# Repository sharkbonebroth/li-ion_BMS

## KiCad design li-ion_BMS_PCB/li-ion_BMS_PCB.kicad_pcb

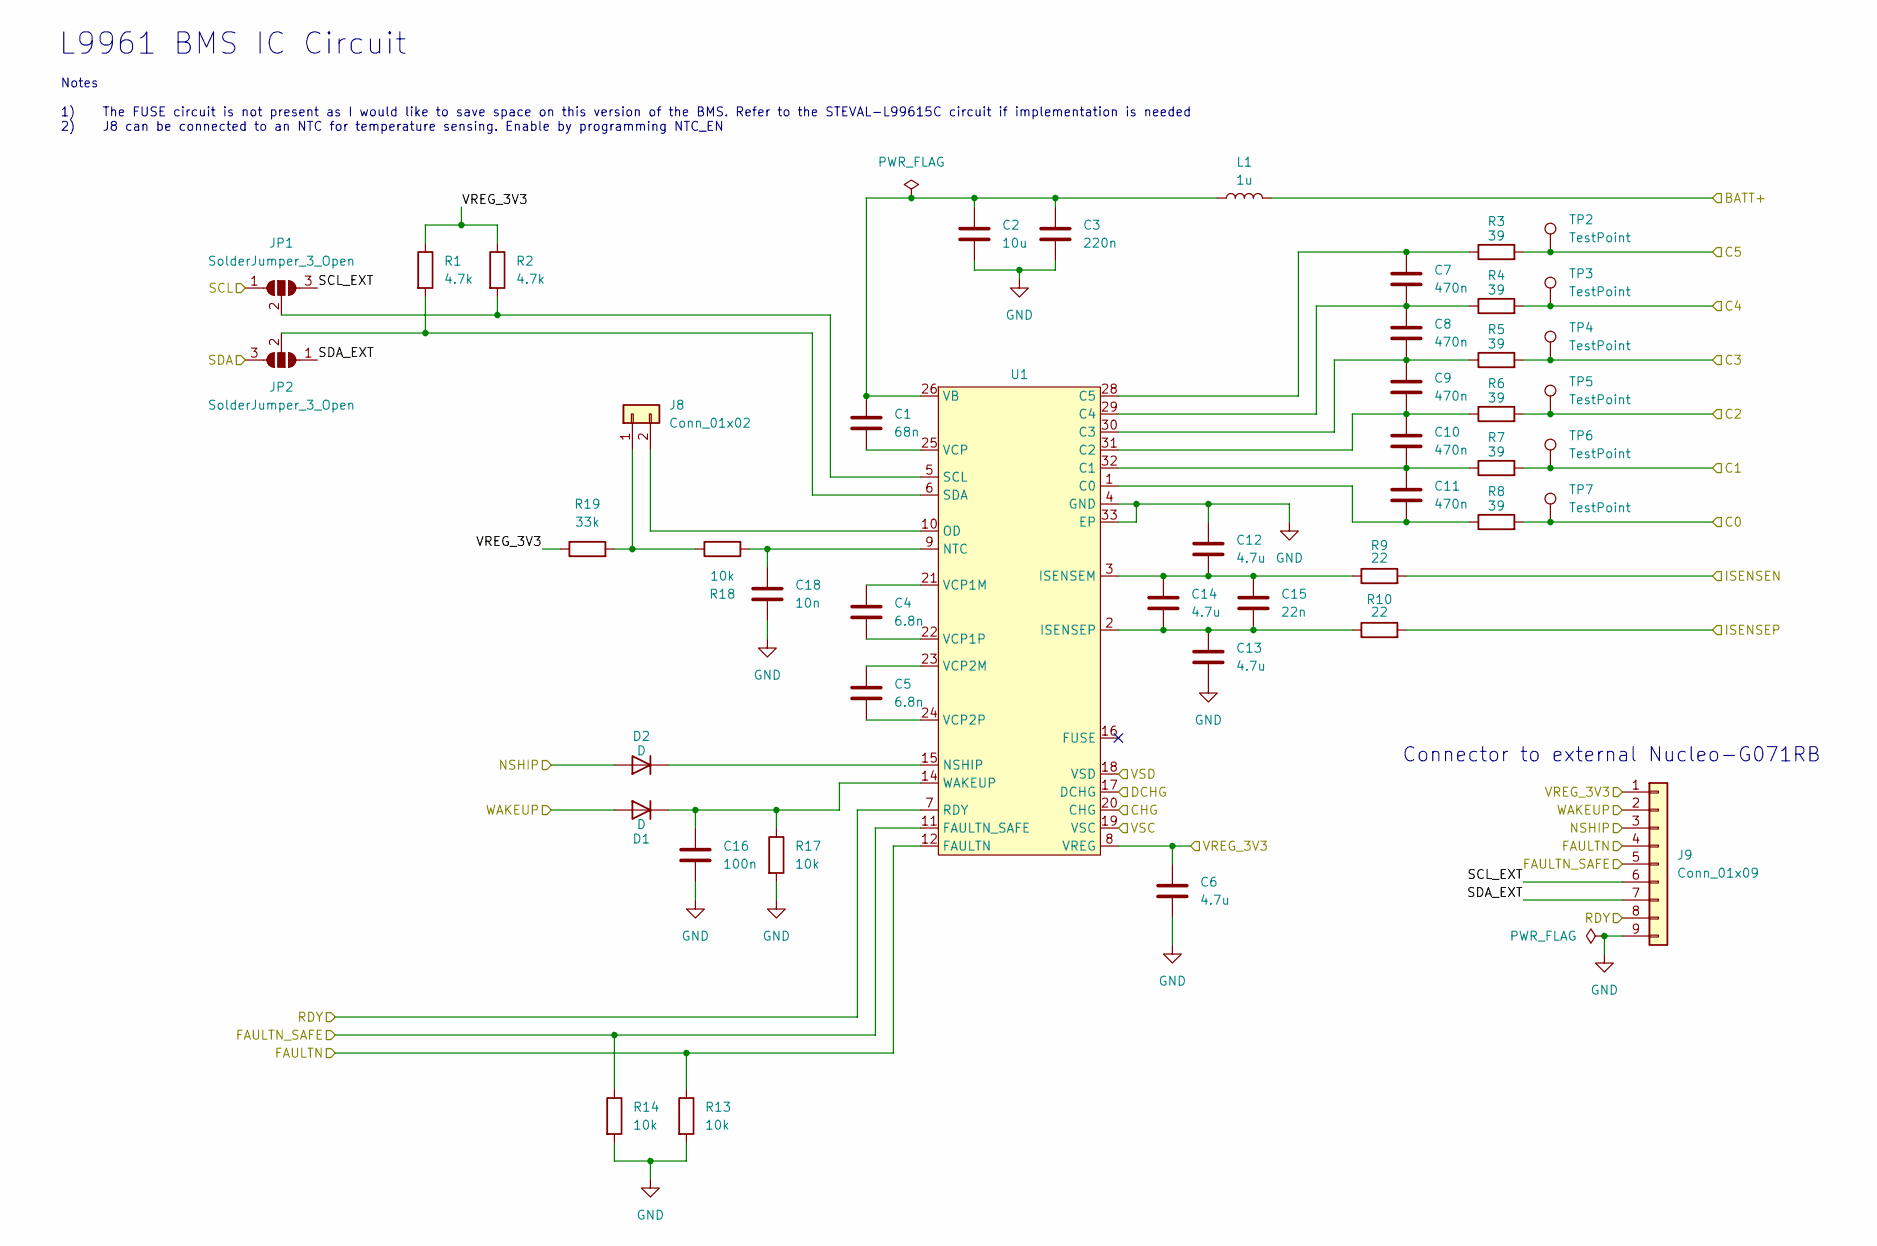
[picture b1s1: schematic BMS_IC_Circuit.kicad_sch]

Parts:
C1: 68n; C_0603_1608Metric; LCSC C31658
C2: 10u; C_0805_2012Metric; LCSC C440198
C3: 220n; C_0805_2012Metric; LCSC C5378
C4, C5: 6.8n; C_0402_1005Metric; LCSC C1542
C6, C12, C13, C14: 4.7u; C_0603_1608Metric; LCSC C19666
C7, C8, C9, C10, C11: 470n; C_0603_1608Metric; LCSC C1623
C15: 22n; C_0603_1608Metric; LCSC C21122
C16: 100n; C_0603_1608Metric; LCSC C14663
C18: 10n; C_0402_1005Metric; LCSC C15195
D1, D2: D; SS34; LCSC C8678
J8: Conn_01x02; JST_GH_SM02B-GHS-TB_1x02-1MP_P1.25mm_Horizontal; LCSC C189893
J9: Conn_01x09; PinHeader_1x09_P2.54mm_Vertical
JP1, JP2: SolderJumper_3_Open; SolderJumper-3_P1.3mm_Open_Pad1.0x1.5mm_NumberLabels
L1: 1u; L_1008_2520Metric; LCSC C86091
R1, R2: 4.7k; R_0402_1005Metric; LCSC C25900
R3, R4, R5, R6, R7, R8: 39; R_1206_3216Metric; LCSC C22198
R9, R10: 22; R_0603_1608Metric; LCSC C23345
R13, R14, R17, R18: 10k; R_0402_1005Metric; LCSC C25744
R19: 33k; R_0402_1005Metric; LCSC C25779
TP2, TP3, TP4, TP5, TP6, TP7: TestPoint; TestPoint_Pad_D1.0mm
U1: QFN50P500X500X100-33N-D

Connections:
/BMS_IC_Circuit/BATT+: L1.2, U1.19 (VSC); also elsewhere on the board
/BMS_IC_Circuit/C0: R8.2, TP7.1; also elsewhere on the board
/BMS_IC_Circuit/C1: R7.2, TP6.1; also elsewhere on the board
/BMS_IC_Circuit/C2: R6.2, TP5.1; also elsewhere on the board
/BMS_IC_Circuit/C3: R5.2, TP4.1; also elsewhere on the board
/BMS_IC_Circuit/C4: R4.2, TP3.1; also elsewhere on the board
/BMS_IC_Circuit/C5: R3.2, TP2.1; also elsewhere on the board
/BMS_IC_Circuit/CHG: U1.20 (CHG); also elsewhere on the board
/BMS_IC_Circuit/DCHG: U1.17 (DCHG); also elsewhere on the board
/BMS_IC_Circuit/FAULTN: J9.4, R13.1, U1.12 (FAULTN); also elsewhere on the board
/BMS_IC_Circuit/FAULTN_SAFE: J9.5, R14.1, U1.11 (FAULTN_SAFE); also elsewhere on the board
/BMS_IC_Circuit/NSHIP: D2.2 (A), J9.3; also elsewhere on the board
/BMS_IC_Circuit/RDY: J9.8, U1.7 (RDY); also elsewhere on the board
/BMS_IC_Circuit/SCL: JP1.1 (A); also elsewhere on the board
/BMS_IC_Circuit/SCL_EXT: J9.6, JP1.3 (B)
/BMS_IC_Circuit/SDA: JP2.3 (B); also elsewhere on the board
/BMS_IC_Circuit/SDA_EXT: J9.7, JP2.1 (A)
/BMS_IC_Circuit/VREG_3V3: C6.1, J9.1, R1.1, R2.1, R19.1, U1.8 (VREG); also elsewhere on the board
/BMS_IC_Circuit/WAKEUP: D1.2 (A), J9.2; also elsewhere on the board
/Battery_Interfacing_Circuit/CHG/DCHG+: U1.18 (VSD); also elsewhere on the board
/Battery_Interfacing_Circuit/CHG/DCHG-: R10.2; also elsewhere on the board
GND: C2.2, C3.2, C6.2, C12.1, C13.2, C16.2, C18.2, J9.9, R9.2, R13.2, R14.2, R17.2, U1.4 (GND), U1.13 (GND), U1.27 (GND), U1.33 (EP); also elsewhere on the board
unnamed: C16.1, D1.1 (K), R17.1, U1.14 (WAKEUP)
unnamed: D2.1 (K), U1.15 (NSHIP)
unnamed: J8.1, R18.1, R19.2
unnamed: J8.2, U1.10 (OD)
unnamed: JP1.2 (C), R2.2, U1.5 (SCL)
unnamed: JP2.2 (C), R1.2, U1.6 (SDA)
unnamed: C11.2, R8.1, U1.1 (C0)
unnamed: C10.2, C11.1, R7.1, U1.32 (C1)
unnamed: C9.2, C10.1, R6.1, U1.31 (C2)
unnamed: C8.2, C9.1, R5.1, U1.30 (C3)
unnamed: C7.2, C8.1, R4.1, U1.29 (C4)
unnamed: C7.1, R3.1, U1.28 (C5)
unnamed: C12.2, C14.1, C15.1, R9.1, U1.3 (ISENSEM)
unnamed: C13.1, C14.2, C15.2, R10.1, U1.2 (ISENSEP)
unnamed: C18.1, R18.2, U1.9 (NTC)
unnamed: C1.1, C2.1, C3.1, L1.1, U1.26 (VB)
unnamed: C4.1, U1.21 (VCP1M)
unnamed: C4.2, U1.22 (VCP1P)
unnamed: C5.1, U1.23 (VCP2M)
unnamed: C5.2, U1.24 (VCP2P)
unnamed: C1.2, U1.25 (VCP)

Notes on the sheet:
L9961 BMS IC Circuit
Notes 1) The FUSE circuit is not present as I would like to save space on this version of the BMS. Refer to the STEVAL-L99615C circuit if implementation is needed 2) J8 can be connected to an NTC for temperature sensing. Enable by programming NTC_EN
Connector to external Nucleo-G071RB

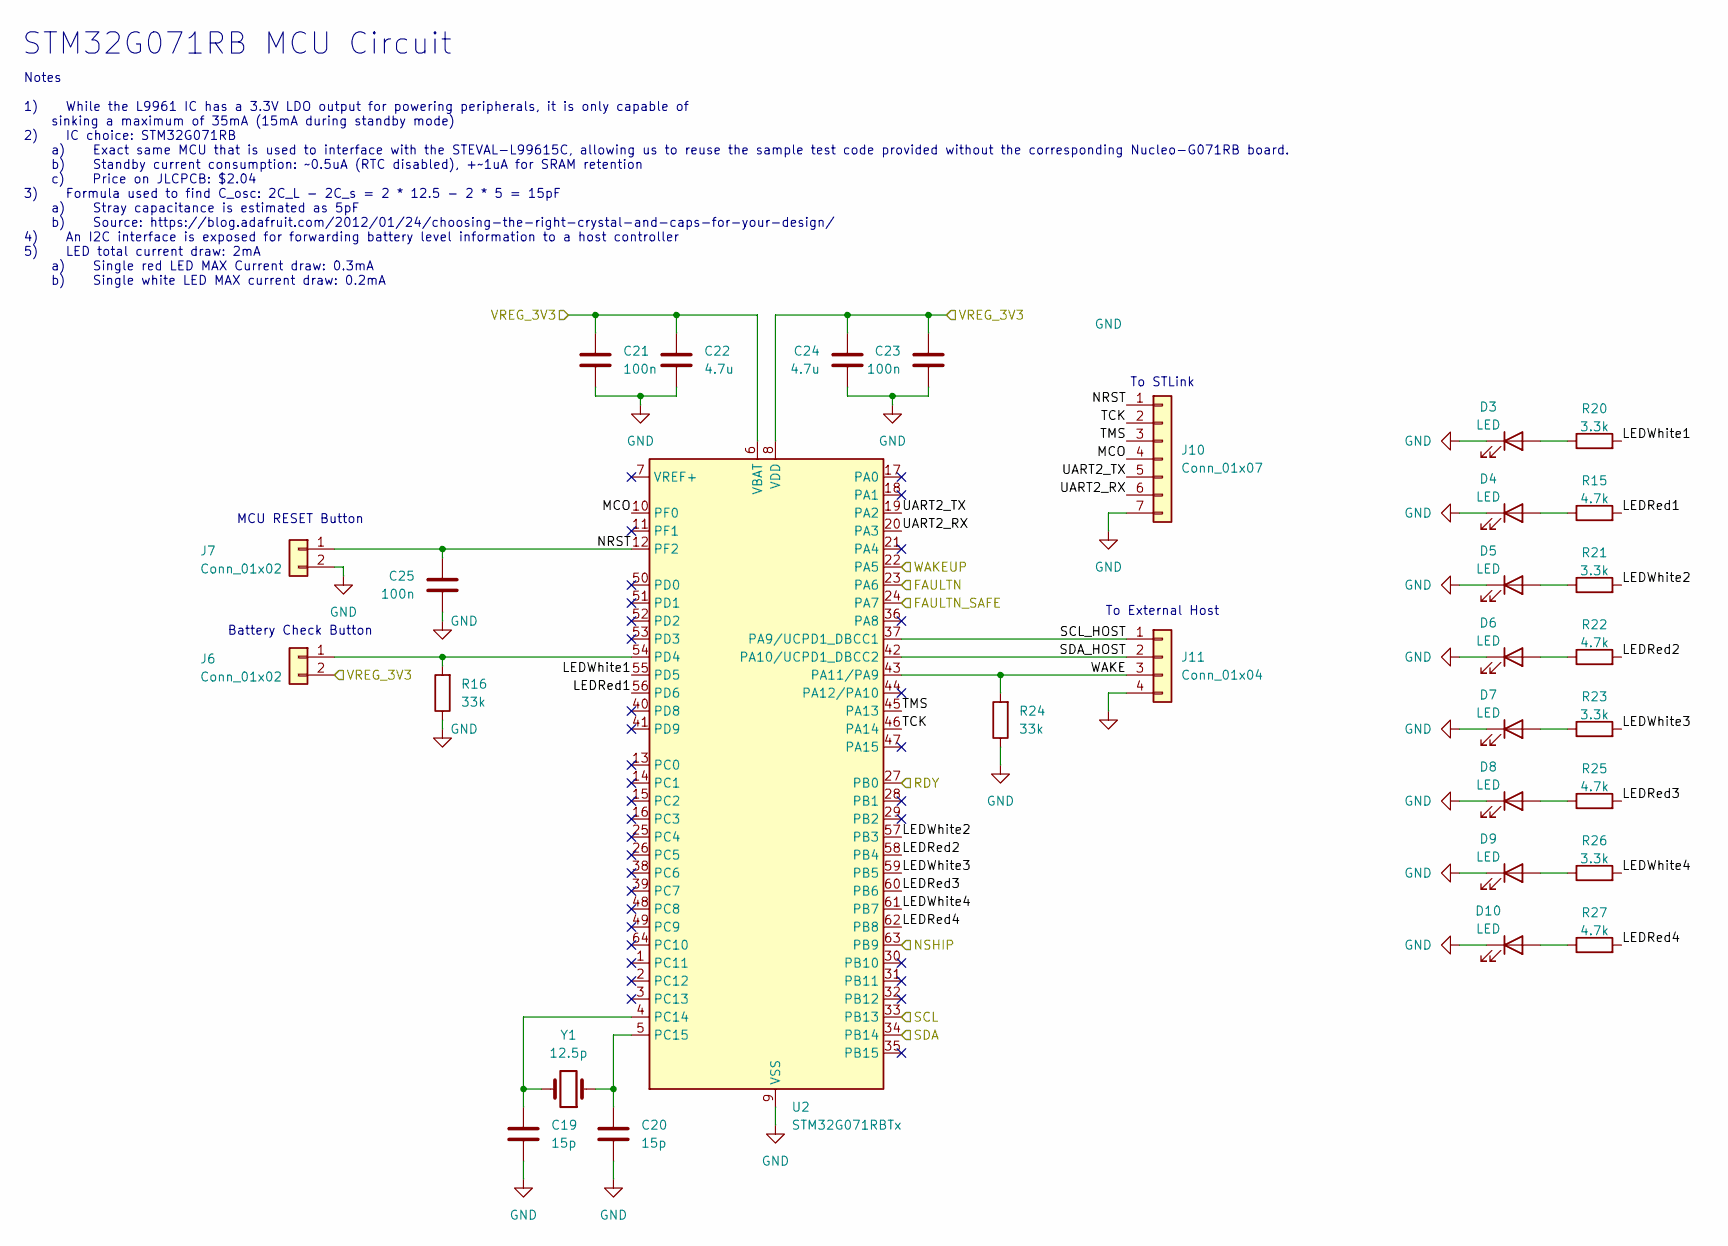
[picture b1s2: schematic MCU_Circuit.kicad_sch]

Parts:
C19, C20: 15p; C_0603_1608Metric; LCSC C1644
C21, C23, C25: 100n; C_0402_1005Metric; LCSC C1525
C22, C24: 4.7u; C_0603_1608Metric; LCSC C19666
D3, D5, D7, D9: LED; LED_0603_1608Metric; LCSC C2290
D4, D6, D8, D10: LED; LED_0603_1608Metric; LCSC C2286
J6, J7: Conn_01x02; JST_GH_SM02B-GHS-TB_1x02-1MP_P1.25mm_Horizontal; LCSC C189893
J10: Conn_01x07; PinHeader_1x07_P2.54mm_Vertical
J11: Conn_01x04; JST_GH_SM04B-GHS-TB_1x04-1MP_P1.25mm_Horizontal; LCSC C189895
R15, R22, R25, R27: 4.7k; R_0402_1005Metric; LCSC C25900
R16, R24: 33k; R_0402_1005Metric; LCSC C25779
R20, R21, R23, R26: 3.3k; R_0402_1005Metric; LCSC C25890
U2: STM32G071RBTx; LQFP-64_10x10mm_P0.5mm; LCSC C432213
Y1: 12.5p; NX3215SA-32.768K-STD-MUA-8; LCSC C156245

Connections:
/BMS_IC_Circuit/FAULTN: U2.23 (PA6); also elsewhere on the board
/BMS_IC_Circuit/FAULTN_SAFE: U2.24 (PA7); also elsewhere on the board
/BMS_IC_Circuit/NSHIP: U2.63 (PB9); also elsewhere on the board
/BMS_IC_Circuit/RDY: U2.27 (PB0); also elsewhere on the board
/BMS_IC_Circuit/SCL: U2.33 (PB13); also elsewhere on the board
/BMS_IC_Circuit/SDA: U2.34 (PB14); also elsewhere on the board
/BMS_IC_Circuit/VREG_3V3: C21.1, C22.1, C23.1, C24.1, J6.2, U2.6 (VBAT), U2.8 (VDD); also elsewhere on the board
/BMS_IC_Circuit/WAKEUP: U2.22 (PA5); also elsewhere on the board
/MCU_Circuit/LEDRed1: R15.2, U2.56 (PD6)
/MCU_Circuit/LEDRed2: R22.2, U2.58 (PB4)
/MCU_Circuit/LEDRed3: R25.2, U2.60 (PB6)
/MCU_Circuit/LEDRed4: R27.2, U2.62 (PB8)
/MCU_Circuit/LEDWhite1: R20.2, U2.55 (PD5)
/MCU_Circuit/LEDWhite2: R21.2, U2.57 (PB3)
/MCU_Circuit/LEDWhite3: R23.2, U2.59 (PB5)
/MCU_Circuit/LEDWhite4: R26.2, U2.61 (PB7)
/MCU_Circuit/MCO: J10.4, U2.10 (PF0)
/MCU_Circuit/NRST: C25.1, J7.1, J10.1, U2.12 (PF2)
/MCU_Circuit/SCL_HOST: J11.1, U2.37 (PA9/UCPD1_DBCC1)
/MCU_Circuit/SDA_HOST: J11.2, U2.42 (PA10/UCPD1_DBCC2)
/MCU_Circuit/TCK: J10.2, U2.46 (PA14)
/MCU_Circuit/TMS: J10.3, U2.45 (PA13)
/MCU_Circuit/UART2_RX: J10.6, U2.20 (PA3)
/MCU_Circuit/UART2_TX: J10.5, U2.19 (PA2)
/MCU_Circuit/WAKE: J11.3, R24.2, U2.43 (PA11/PA9)
GND: C19.2, C20.2, C21.2, C22.2, C23.2, C24.2, C25.2, D3.1 (K), D4.1 (K), D5.1 (K), D6.1 (K), D7.1 (K), D8.1 (K), D9.1 (K), D10.1 (K), J7.2, J10.7, J11.4, R16.1, R24.1, U2.9 (VSS); also elsewhere on the board
unnamed: D3.2 (A), R20.1
unnamed: D4.2 (A), R15.1
unnamed: D5.2 (A), R21.1
unnamed: D6.2 (A), R22.1
unnamed: D7.2 (A), R23.1
unnamed: D8.2 (A), R25.1
unnamed: D9.2 (A), R26.1
unnamed: D10.2 (A), R27.1
unnamed: J6.1, R16.2, U2.54 (PD4)
unnamed: C19.1, U2.4 (PC14), Y1.2
unnamed: C20.1, U2.5 (PC15), Y1.1

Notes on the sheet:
MCU RESET Button
STM32G071RB MCU Circuit
Battery Check Button
To External Host
To STLink
Notes 1) While the L9961 IC has a 3.3V LDO output for powering peripherals, it is only capable of sinking a maximum of 35mA (15mA during standby mode) 2) IC choice: STM32G071RB a) Exact same MCU that is used to interface with the STEVAL-L99615C, allowing us to reuse the sample test code provided wi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

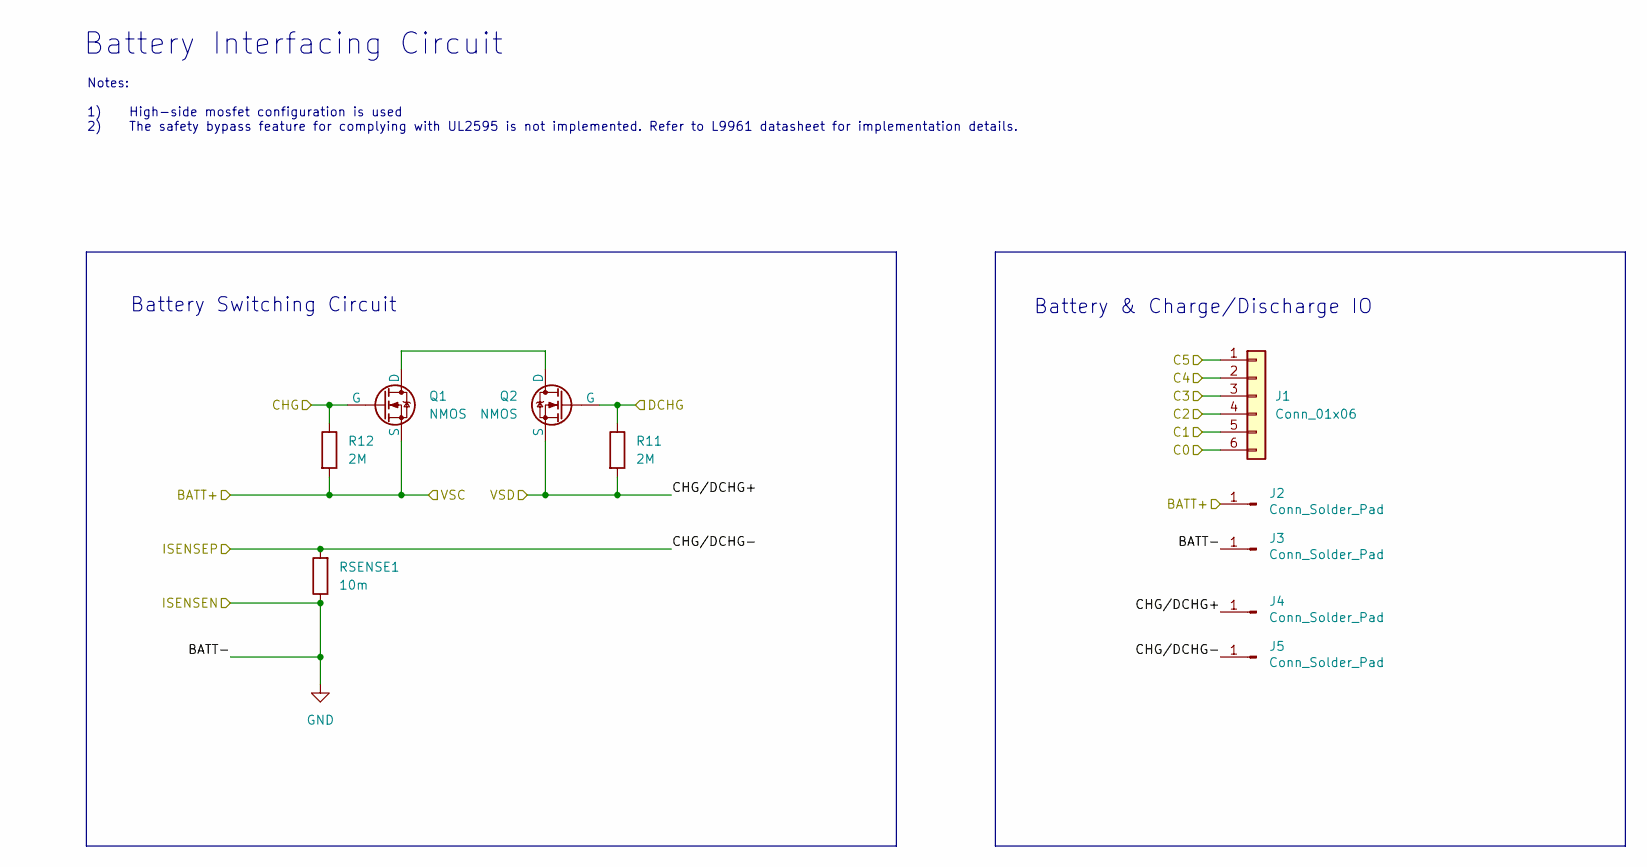
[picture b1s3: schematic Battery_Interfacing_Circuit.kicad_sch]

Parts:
J1: Conn_01x06; JST_GH_SM06B-GHS-TB_1x06-1MP_P1.25mm_Horizontal; LCSC C133065
J2, J3, J4, J5: Conn_Solder_Pad; SolderWire-0.75sqmm_1x01_D1.25mm_OD2.3mm
Q1, Q2: NMOS; JLCPCB-DFN-8(4.9x5.8); LCSC C78118
R11, R12: 2M; R_0603_1608Metric; LCSC C22976
RSENSE1: 10m; R_2512_6332Metric; LCSC C393072

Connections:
/BMS_IC_Circuit/BATT+: J2.1, Q1.3 (S), R12.2; also elsewhere on the board
/BMS_IC_Circuit/C0: J1.6; also elsewhere on the board
/BMS_IC_Circuit/C1: J1.5; also elsewhere on the board
/BMS_IC_Circuit/C2: J1.4; also elsewhere on the board
/BMS_IC_Circuit/C3: J1.3; also elsewhere on the board
/BMS_IC_Circuit/C4: J1.2; also elsewhere on the board
/BMS_IC_Circuit/C5: J1.1; also elsewhere on the board
/BMS_IC_Circuit/CHG: Q1.2 (G), R12.1; also elsewhere on the board
/BMS_IC_Circuit/DCHG: Q2.2 (G), R11.1; also elsewhere on the board
/Battery_Interfacing_Circuit/CHG/DCHG+: J4.1, Q2.3 (S), R11.2; also elsewhere on the board
/Battery_Interfacing_Circuit/CHG/DCHG-: J5.1, RSENSE1.2; also elsewhere on the board
GND: J3.1, RSENSE1.1; also elsewhere on the board
unnamed: Q1.1 (D), Q2.1 (D)

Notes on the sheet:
Battery Switching Circuit
Notes: 1) High-side mosfet configuration is used 2) The safety bypass feature for complying with UL2595 is not implemented. Refer to L9961 datasheet for implementation details.
Battery Interfacing Circuit
Battery & Charge/Discharge IO

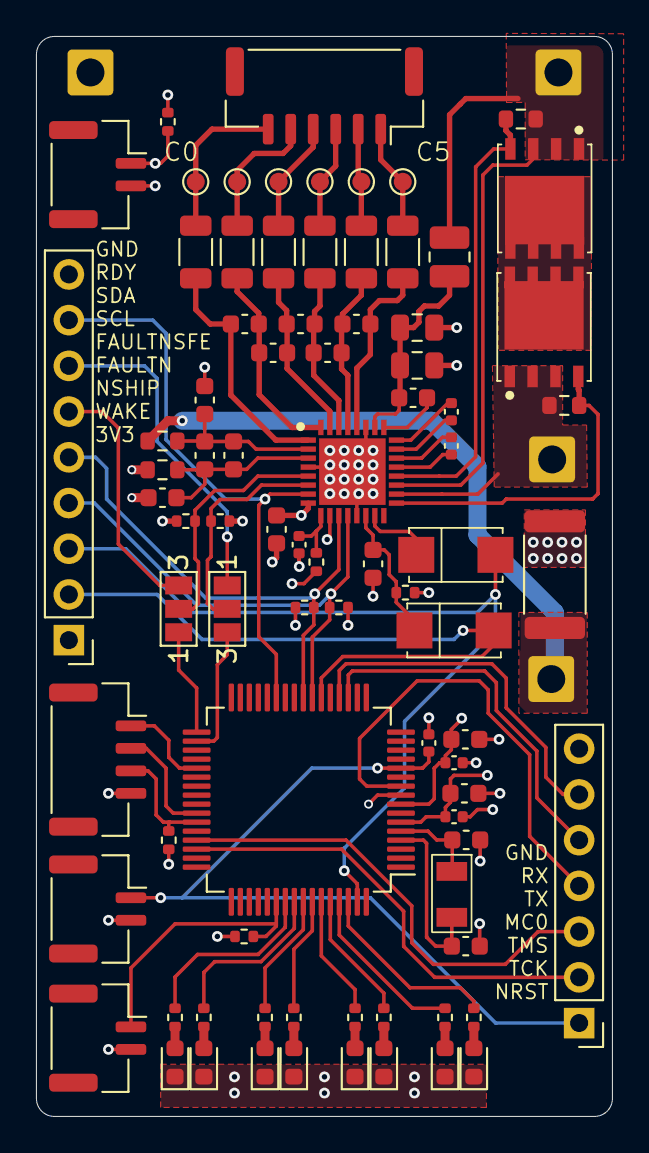
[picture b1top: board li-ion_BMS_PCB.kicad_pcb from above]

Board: 4 copper layers, 32.0 x 60.0 mm, 87 parts (0 on the bottom side), 72 nets.

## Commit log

2025-03-31 finished L9961 Wiring
2025-04-25 progress
2025-04-29 finished initial V1
